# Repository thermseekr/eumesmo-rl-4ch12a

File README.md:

# eumesmo-rl-4ch12a

Relay board with 4x 24 VDC NO relays. This board is designed to be used togheter with [eumesmo-io-24v16ch](https://github.com/thermseekr/eumesmo-io-24v16ch), but can be driven by any 24V control circuit compatible with NPN inputs. It uses Omron 16A relays and is limited to 12A/channel per copper trace capacity.

The board is compatible with the SP7 DIN rail system from Metaltex.

VERSION HISTORY

V1.2 - 2026/06/13 - Repository renamed from RELAY-24V-4CH-12A to eumesmo-rl-4ch12A to align the design with the eumesmo line of building automation products.

V1.1 - 2026/06/02 - Input terminal blocks replaced from 2.54mm to 3.5mm pitch for easier installation in the field.

V1.0 - 2025/12/19 - Initial release.

## LICENSE

This project is licensed under the [Creative Commons BY-NC 4.0 License](https://creativecommons.org/licenses/by-nc/4.0/).
Commercial use is not permitted without prior written consent. See the [LICENSE.txt](LICENSE.txt) file for details.

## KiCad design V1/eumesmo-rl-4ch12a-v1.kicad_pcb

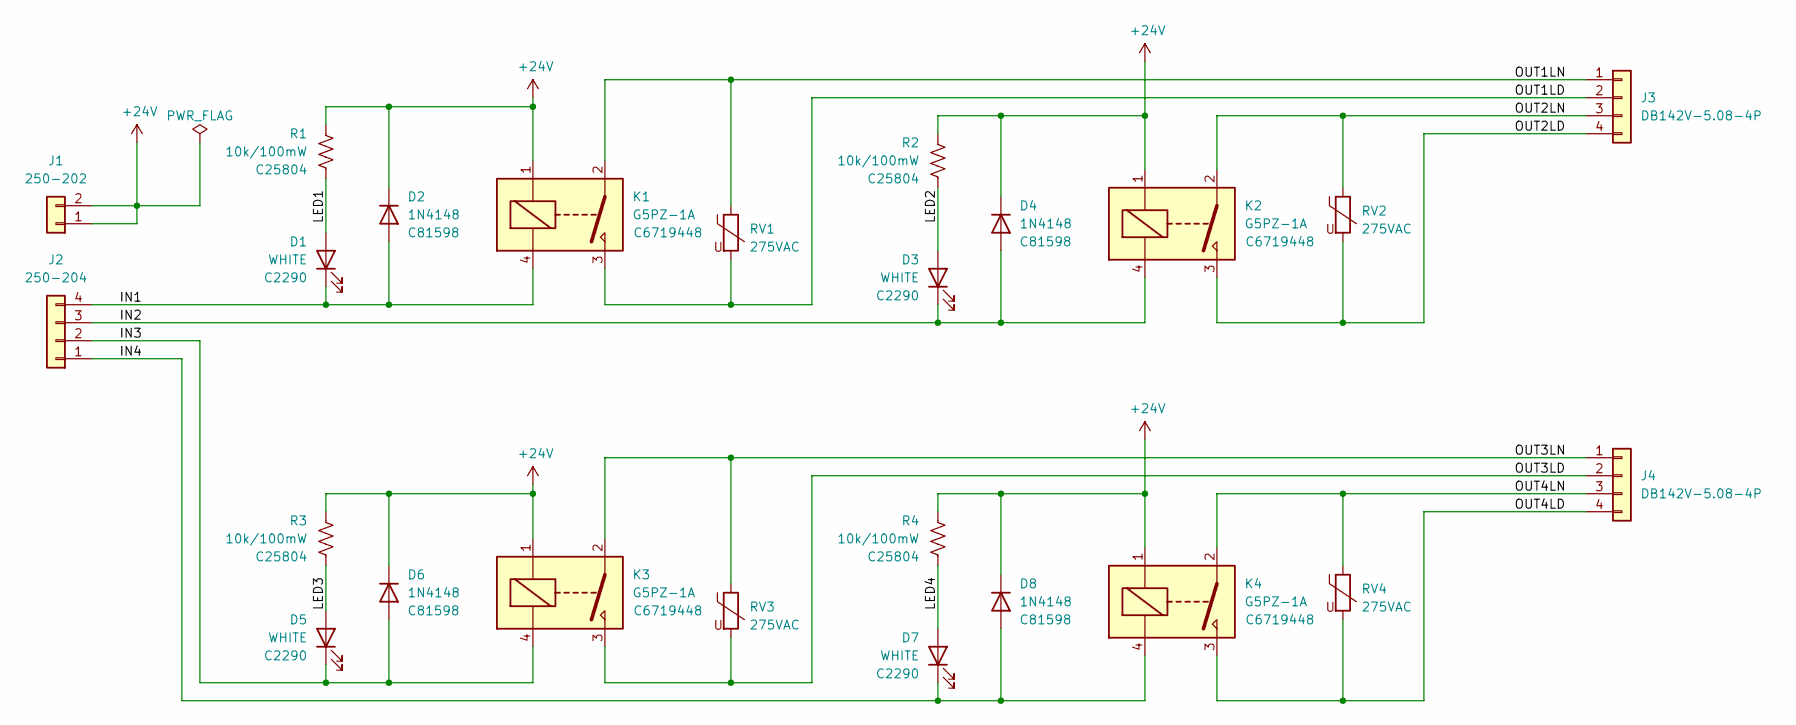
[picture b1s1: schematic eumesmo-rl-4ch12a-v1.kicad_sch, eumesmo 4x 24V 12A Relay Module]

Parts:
D1, D3, D5, D7: WHITE; LED_0603_1608Metric; Mfr PN KT-0603W; LCSC Part # C2290
D2, D4, D6, D8: 1N4148; D_SOD-123; Mfr PN 1N4148W; LCSC Part # C81598
J1: 250-202; TerminalBlock_Wago_250-202_1x02_P3.5mm_45Degree; Mfr PN 250-202; JLCPCB BOM 1
J2: 250-204; TerminalBlock_Wago_250-204_1x04_P3.5mm_45Degree; Mfr PN 250-204; JLCPCB BOM 1
J3, J4: DB142V-5.08-4P; TerminalBlock_Dibo_DB142V-5.08-4P_1x04_P5.08mm_Vertical; Mfr PN DB142V-5.08-4P-GN; JLCPCB BOM 1
K1, K2, K3, K4: G5PZ-1A; Relay_SPST_Omron_G5PZ-1A; Mfr PN G5PZ-1A-E DC24V; JLCPCB BOM 1
R1, R2, R3, R4: 10k/100mW; R_0603_1608Metric; Mfr PN 0603WAF1002T5E; LCSC Part # C25804
RV1, RV2, RV3, RV4: 275VAC; RV_Disc_D9.50mm_W3.6mm_P5.08mm; Mfr PN RM07D431KC1IE100; JLCPCB BOM 1

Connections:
+24V: D2.1 (K), D4.1 (K), D6.1 (K), D8.1 (K), J1.1, J1.2, K1.1, K2.1, K3.1, K4.1, R1.1, R2.1, R3.1, R4.1
/IN1: D1.1 (K), D2.2 (A), J2.4, K1.4
/IN2: D3.1 (K), D4.2 (A), J2.3, K2.4
/IN3: D5.1 (K), D6.2 (A), J2.2, K3.4
/IN4: D7.1 (K), D8.2 (A), J2.1, K4.4
/LED1: D1.2 (A), R1.2
/LED2: D3.2 (A), R2.2
/LED3: D5.2 (A), R3.2
/LED4: D7.2 (A), R4.2
/OUT1LD: J3.2, K1.3, RV1.2
/OUT1LN: J3.1, K1.2, RV1.1
/OUT2LD: J3.4, K2.3, RV2.2
/OUT2LN: J3.3, K2.2, RV2.1
/OUT3LD: J4.2, K3.3, RV3.2
/OUT3LN: J4.1, K3.2, RV3.1
/OUT4LD: J4.4, K4.3, RV4.2
/OUT4LN: J4.3, K4.2, RV4.1

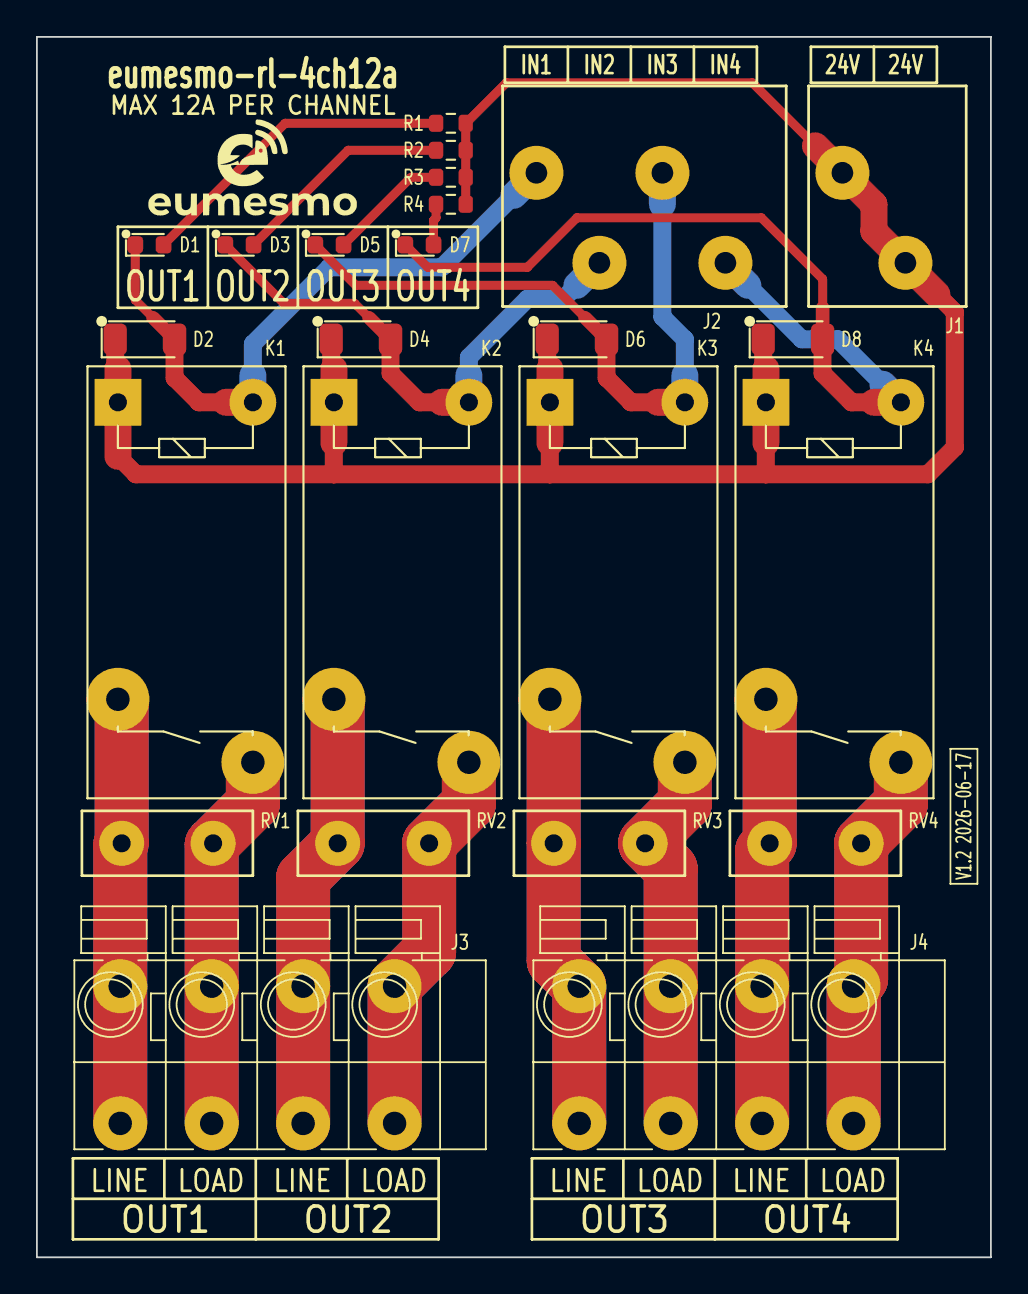
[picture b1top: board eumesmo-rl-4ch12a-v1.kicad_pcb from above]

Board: 2 copper layers, 53.0 x 67.8 mm, 24 parts (0 on the bottom side), 17 nets.

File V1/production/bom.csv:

Designator,Footprint,Quantity,Value,LCSC Part #
"D1, D3, D5, D7",0603,4,WHITE,C2290
"D2, D4, D6, D8",D_SOD-123,4,1N4148,C81598
J1,TerminalBlock_Wago_250-202_1x02_P3.5mm_45Degree,1,250-202,C2765061
J2,TerminalBlock_Wago_250-204_1x04_P3.5mm_45Degree,1,250-204,C2765063
"J3, J4",TerminalBlock_Dibo_DB142V-5.08-4P_1x04_P5.08mm_Vertical,2,DB142V-5.08-4P,C2898701
"K1, K2, K3, K4",Relay_SPST_Omron_G5PZ-1A,4,G5PZ-1A,C6719448
"R1, R2, R3, R4",0603,4,10k/100mW,C25804
"RV1, RV2, RV3, RV4",RV_Disc_D9.50mm_W3.6mm_P5.08mm,4,275VAC,C2761646

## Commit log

2026-06-02 Replaced terminal blocks
2026-06-02 File renamed
2026-06-02 Replaced terminal block
2026-06-02 Silkscreen updated
2026-06-02 Image updated
2026-06-02 Adjusted file naming convention
2026-06-12 Replaced input terminal blocks for 3.5mm pitch.
2026-06-13 Old releases moved to oldreleases folder
2026-06-13 Fix image caption in README.md
2026-06-13 Update README with version history changes
    Updated version history to reflect repository renaming and changes.
2026-06-13 Adjusted version number
2026-06-13 Adjusted product name on the silkscreen
2026-06-17 Release V1.2.0
